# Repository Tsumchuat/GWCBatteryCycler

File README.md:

This is a WIP device to discharge and recharge (cycle) up to 4 Greenpower F24 (Yuasa REC 36) batteries at once. It is also capable of measuring the battery capacity.

This repo, account and code is not associated with GWC

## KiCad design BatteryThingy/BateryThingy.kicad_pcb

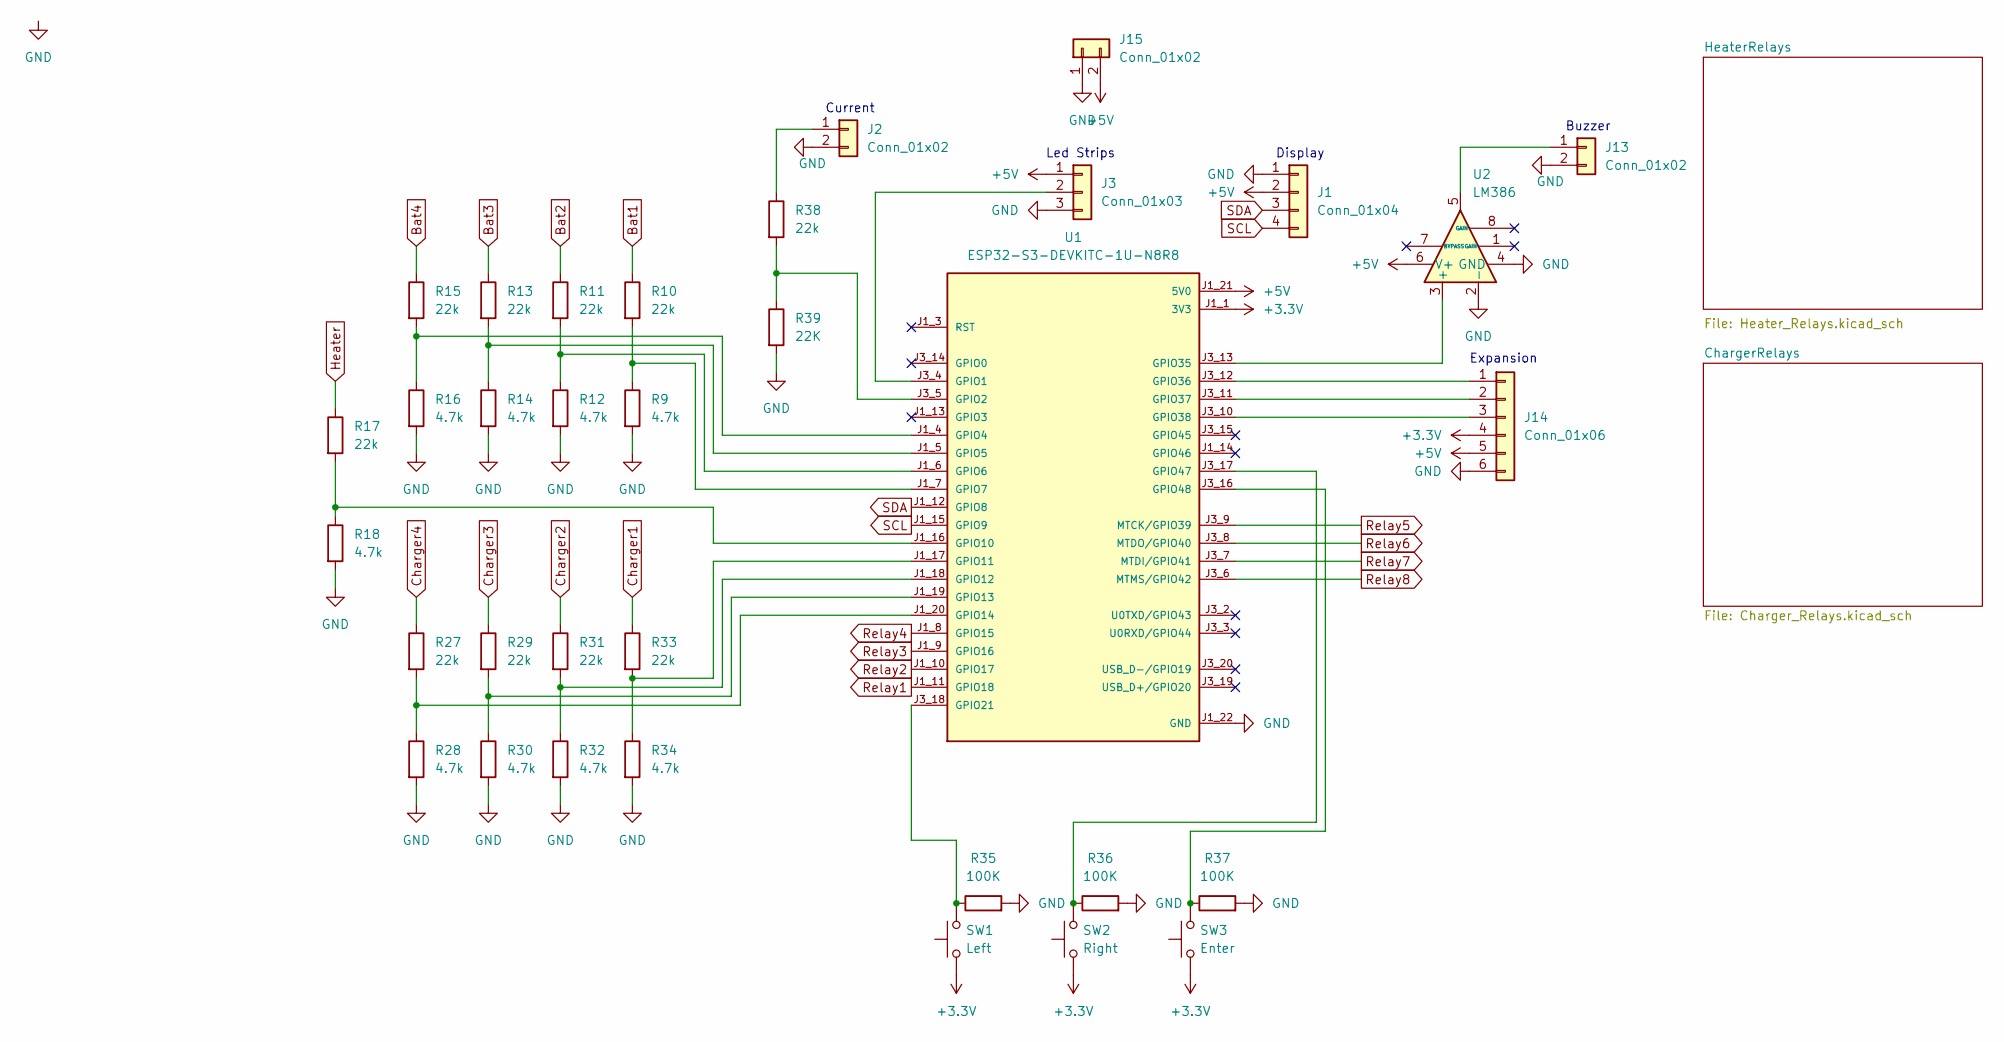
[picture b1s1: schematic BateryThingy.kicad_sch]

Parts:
J1: Conn_01x04; PinHeader_1x04_P2.54mm_Vertical
J2, J13, J15: Conn_01x02; PinHeader_1x02_P2.54mm_Vertical
J3: Conn_01x03; PinHeader_1x03_P2.54mm_Vertical
J14: Conn_01x06; PinHeader_1x06_P2.54mm_Vertical
R9, R12, R14, R16, R18, R28, R30, R32, R34: 4.7k; R_Axial_DIN0411_L9.9mm_D3.6mm_P12.70mm_Horizontal
R10, R11, R13, R15, R17, R27, R29, R31, R33, R38: 22k; R_Axial_DIN0411_L9.9mm_D3.6mm_P12.70mm_Horizontal
R35, R36, R37: 100K; R_Axial_DIN0411_L9.9mm_D3.6mm_P12.70mm_Horizontal
R39: 22K; R_Axial_DIN0411_L9.9mm_D3.6mm_P12.70mm_Horizontal
SW1: Left; SW_PUSH_6mm
SW2: Right; SW_PUSH_6mm
SW3: Enter; SW_PUSH_6mm
U1: ESP32-S3-DEVKITC-1U-N8R8; MODULE_ESP32-S3-DEVKITC-1U-N8R8; PARTREV 1.1
U2: LM386; DIP08

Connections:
+3.3V: J14.4, SW1.1, SW2.1, SW3.1, U1.J1_1 (3V3), U1.J1_2 (3V3)
+5V: J1.2, J3.1, J14.5, J15.2, U1.J1_21 (5V0), U2.6 (V+); also elsewhere on the board
Bat1: R10.1; also elsewhere on the board
Bat2: R11.1; also elsewhere on the board
Bat3: R13.1; also elsewhere on the board
Bat4: R15.1; also elsewhere on the board
Charger1: R33.1; also elsewhere on the board
Charger2: R31.1; also elsewhere on the board
Charger3: R29.1; also elsewhere on the board
Charger4: R27.1; also elsewhere on the board
GND: J1.1, J2.2, J3.3, J13.2, J14.6, J15.1, R9.2, R12.2, R14.2, R16.2, R18.2, R28.2, R30.2, R32.2, R34.2, R35.2, R36.2, R37.2, R39.2, U1.J1_22 (GND), U1.J3_1 (GND), U1.J3_21 (GND), U1.J3_22 (GND), U2.2 (-), U2.4 (GND); also elsewhere on the board
Heater: R17.1; also elsewhere on the board
unnamed: J2.1, R38.1
unnamed: J3.2, U1.J3_4 (GPIO1)
unnamed: J13.1, U2.5
unnamed: J14.1, U1.J3_12 (GPIO36)
unnamed: J14.2, U1.J3_11 (GPIO37)
unnamed: J14.3, U1.J3_10 (GPIO38)
unnamed: R38.2, R39.1, U1.J3_5 (GPIO2)
unnamed: R15.2, R16.1, U1.J1_4 (GPIO4)
unnamed: R13.2, R14.1, U1.J1_5 (GPIO5)
unnamed: R11.2, R12.1, U1.J1_6 (GPIO6)
unnamed: R9.1, R10.2, U1.J1_7 (GPIO7)
unnamed: R17.2, R18.1, U1.J1_16 (GPIO10)
unnamed: R33.2, R34.1, U1.J1_17 (GPIO11)
unnamed: R31.2, R32.1, U1.J1_18 (GPIO12)
unnamed: R29.2, R30.1, U1.J1_19 (GPIO13)
unnamed: R27.2, R28.1, U1.J1_20 (GPIO14)
unnamed: R35.1, SW1.2, U1.J3_18 (GPIO21)
unnamed: U1.J3_13 (GPIO35), U2.3 (+)
unnamed: R36.1, SW2.2, U1.J3_17 (GPIO47)
unnamed: R37.1, SW3.2, U1.J3_16 (GPIO48)
Relay1: U1.J1_11 (GPIO18); also elsewhere on the board
Relay2: U1.J1_10 (GPIO17); also elsewhere on the board
Relay3: U1.J1_9 (GPIO16); also elsewhere on the board
Relay4: U1.J1_8 (GPIO15); also elsewhere on the board
Relay5: U1.J3_9 (MTCK/GPIO39); also elsewhere on the board
Relay6: U1.J3_8 (MTDO/GPIO40); also elsewhere on the board
Relay7: U1.J3_7 (MTDI/GPIO41); also elsewhere on the board
Relay8: U1.J3_6 (MTMS/GPIO42); also elsewhere on the board
SCL: J1.4, U1.J1_15 (GPIO9)
SDA: J1.3, U1.J1_12 (GPIO8)

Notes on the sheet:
Display
Expansion
Current
Buzzer
Led Strips

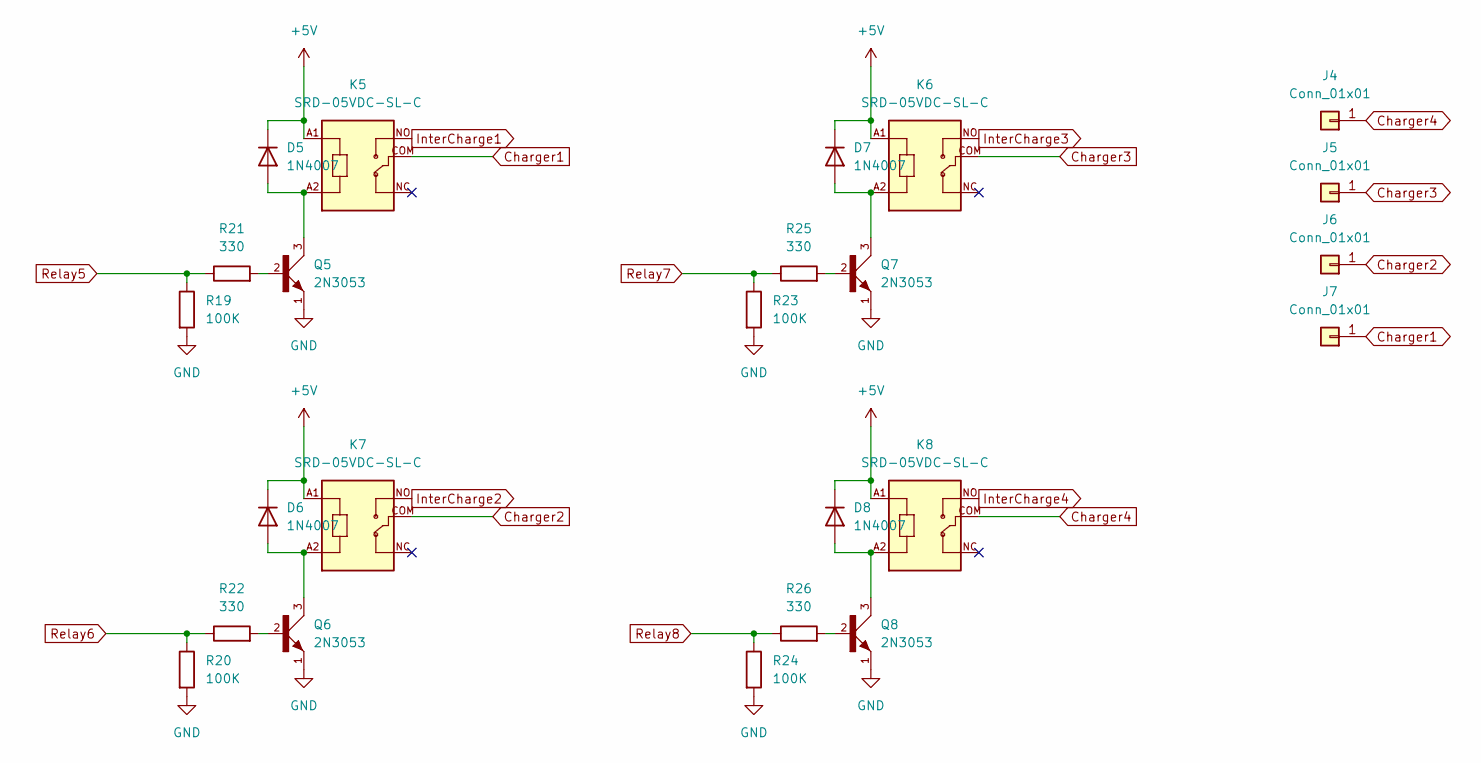
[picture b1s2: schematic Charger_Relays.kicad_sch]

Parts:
D5, D6, D7, D8: 1N4007; D_DO-41_SOD81_P10.16mm_Horizontal
J4, J5, J6, J7: Conn_01x01; SolderWirePad_1x01_SMD_5x10mm
K5, K6, K7, K8: SRD-05VDC-SL-C; RELAY_SRD-05VDC-SL-C
Q5, Q6, Q7, Q8: 2N3053; TO39
R19, R20, R23, R24: 100K; R_Axial_DIN0411_L9.9mm_D3.6mm_P12.70mm_Horizontal
R21, R22, R25, R26: 330; R_Axial_DIN0411_L9.9mm_D3.6mm_P12.70mm_Horizontal

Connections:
+5V: D5.1 (K), D6.1 (K), D7.1 (K), D8.1 (K), K5.A1, K6.A1, K7.A1, K8.A1; also elsewhere on the board
Charger1: J7.1, K5.COM; also elsewhere on the board
Charger2: J6.1, K7.COM; also elsewhere on the board
Charger3: J5.1, K6.COM; also elsewhere on the board
Charger4: J4.1, K8.COM; also elsewhere on the board
GND: Q5.1, Q6.1, Q7.1, Q8.1, R19.2, R20.2, R23.2, R24.2; also elsewhere on the board
InterCharge1: K5.NO; also elsewhere on the board
InterCharge2: K7.NO; also elsewhere on the board
InterCharge3: K6.NO; also elsewhere on the board
InterCharge4: K8.NO; also elsewhere on the board
unnamed: D5.2 (A), K5.A2, Q5.3
unnamed: D6.2 (A), K7.A2, Q6.3
unnamed: D7.2 (A), K6.A2, Q7.3
unnamed: D8.2 (A), K8.A2, Q8.3
unnamed: Q5.2, R21.2
unnamed: Q6.2, R22.2
unnamed: Q7.2, R25.2
unnamed: Q8.2, R26.2
Relay5: R19.1, R21.1; also elsewhere on the board
Relay6: R20.1, R22.1; also elsewhere on the board
Relay7: R23.1, R25.1; also elsewhere on the board
Relay8: R24.1, R26.1; also elsewhere on the board

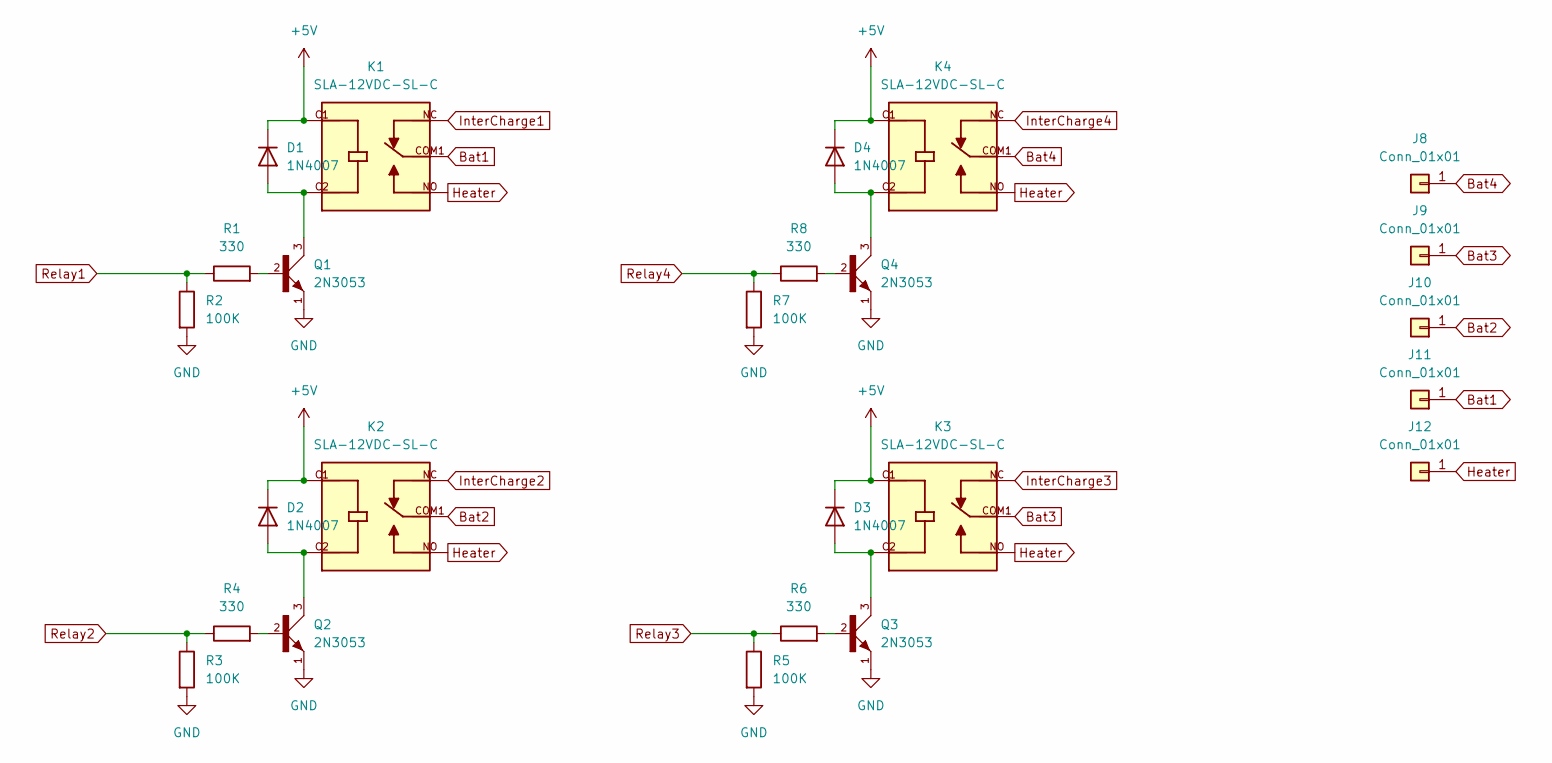
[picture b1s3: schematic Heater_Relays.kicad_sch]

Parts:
D1, D2, D3, D4: 1N4007; D_DO-41_SOD81_P10.16mm_Horizontal
J8, J9, J10, J11, J12: Conn_01x01; SolderWirePad_1x01_SMD_5x10mm
K1, K2, K3, K4: SLA-12VDC-SL-C; RELAY_SLA-12VDC-SL-C
Q1, Q2, Q3, Q4: 2N3053; TO39
R1, R4, R6, R8: 330; R_Axial_DIN0411_L9.9mm_D3.6mm_P12.70mm_Horizontal
R2, R3, R5, R7: 100K; R_Axial_DIN0411_L9.9mm_D3.6mm_P12.70mm_Horizontal

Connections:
+5V: D1.1 (K), D2.1 (K), D3.1 (K), D4.1 (K), K1.C1, K2.C1, K3.C1, K4.C1; also elsewhere on the board
Bat1: J11.1, K1.COM1, K1.COM2; also elsewhere on the board
Bat2: J10.1, K2.COM1, K2.COM2; also elsewhere on the board
Bat3: J9.1, K3.COM1, K3.COM2; also elsewhere on the board
Bat4: J8.1, K4.COM1, K4.COM2; also elsewhere on the board
GND: Q1.1, Q2.1, Q3.1, Q4.1, R2.2, R3.2, R5.2, R7.2; also elsewhere on the board
Heater: J12.1 (Pin_1_1), K1.NO, K2.NO, K3.NO, K4.NO; also elsewhere on the board
InterCharge1: K1.NC; also elsewhere on the board
InterCharge2: K2.NC; also elsewhere on the board
InterCharge3: K3.NC; also elsewhere on the board
InterCharge4: K4.NC; also elsewhere on the board
unnamed: D1.2 (A), K1.C2, Q1.3
unnamed: D2.2 (A), K2.C2, Q2.3
unnamed: D3.2 (A), K3.C2, Q3.3
unnamed: D4.2 (A), K4.C2, Q4.3
unnamed: Q1.2, R1.2
unnamed: Q2.2, R4.2
unnamed: Q3.2, R6.2
unnamed: Q4.2, R8.2
Relay1: R1.1, R2.1; also elsewhere on the board
Relay2: R3.1, R4.1; also elsewhere on the board
Relay3: R5.1, R6.1; also elsewhere on the board
Relay4: R7.1, R8.1; also elsewhere on the board

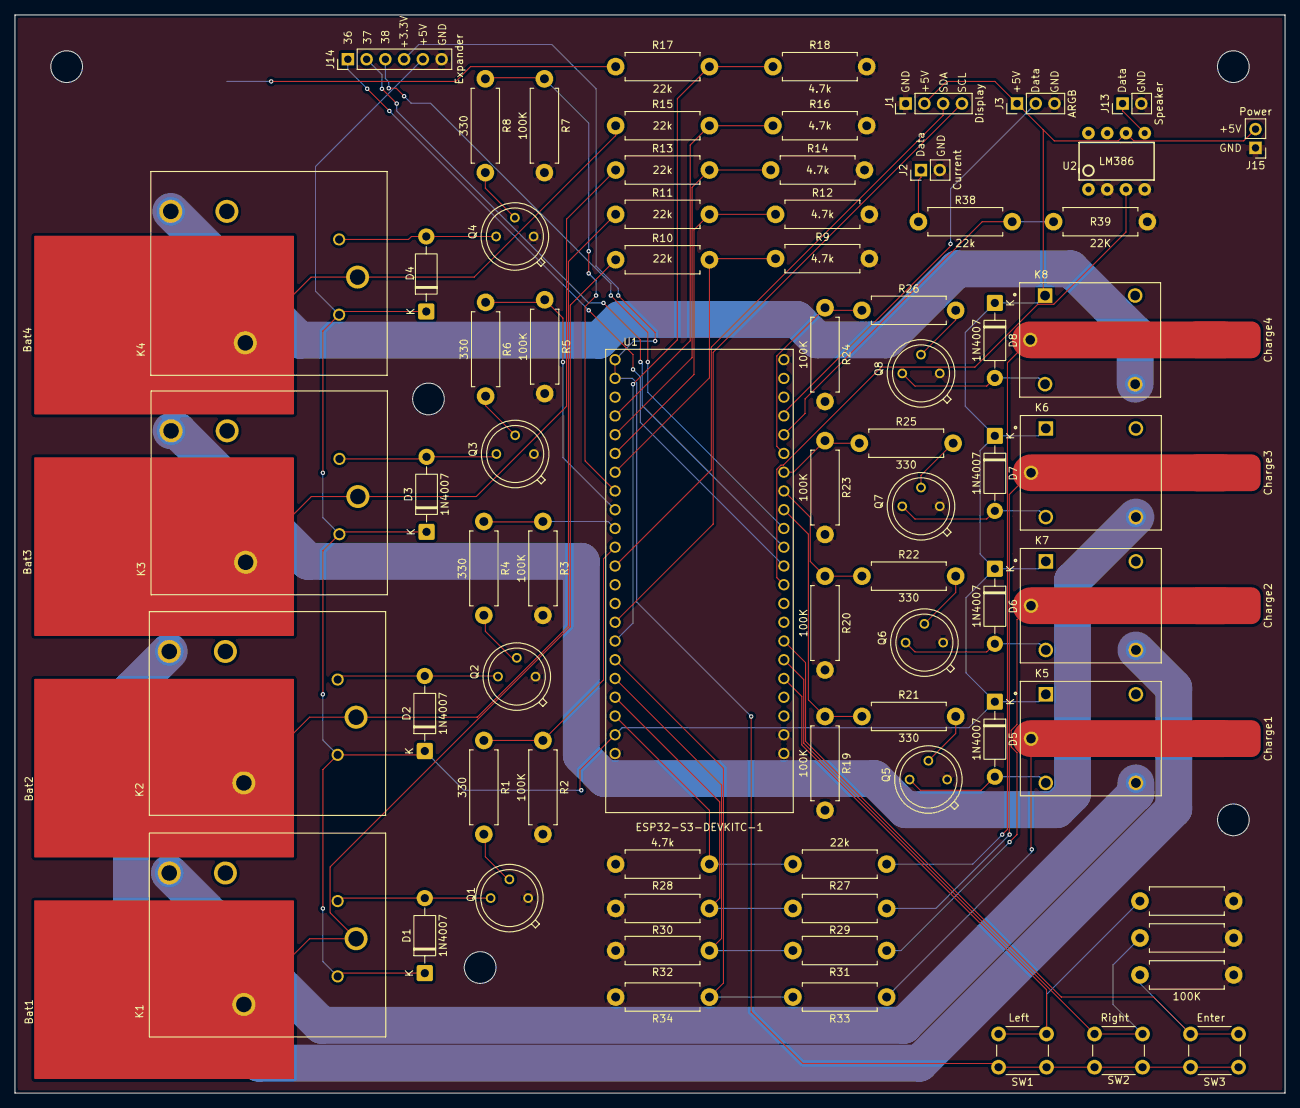
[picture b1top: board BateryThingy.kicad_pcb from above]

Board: 2 copper layers, 172.0 x 146.0 mm, 83 parts (0 on the bottom side), 62 nets.

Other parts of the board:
Bat1, Bat2, Bat3, Bat4: Conn_01x01; SolderWirePad_1x01_SMD_5x10mm
Charge1, Charge2, Charge3, Charge4: Conn_01x01; SolderWirePad_1x01_SMD_5x10mm

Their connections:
Bat1: Bat1.1 (Pin_1_1); also elsewhere on the board
Bat2: Bat2.1 (Pin_1_1); also elsewhere on the board
Bat3: Bat3.1 (Pin_1_1); also elsewhere on the board
Bat4: Bat4.1 (Pin_1_1); also elsewhere on the board
Charger1: Charge1.1 (Pin_1_1); also elsewhere on the board
Charger2: Charge2.1 (Pin_1_1); also elsewhere on the board
Charger3: Charge3.1 (Pin_1_1); also elsewhere on the board
Charger4: Charge4.1 (Pin_1_1); also elsewhere on the board

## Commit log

2026-04-14 Added harware files
